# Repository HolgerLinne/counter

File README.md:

# counter
Fast photon counter

A real README will follow soon !

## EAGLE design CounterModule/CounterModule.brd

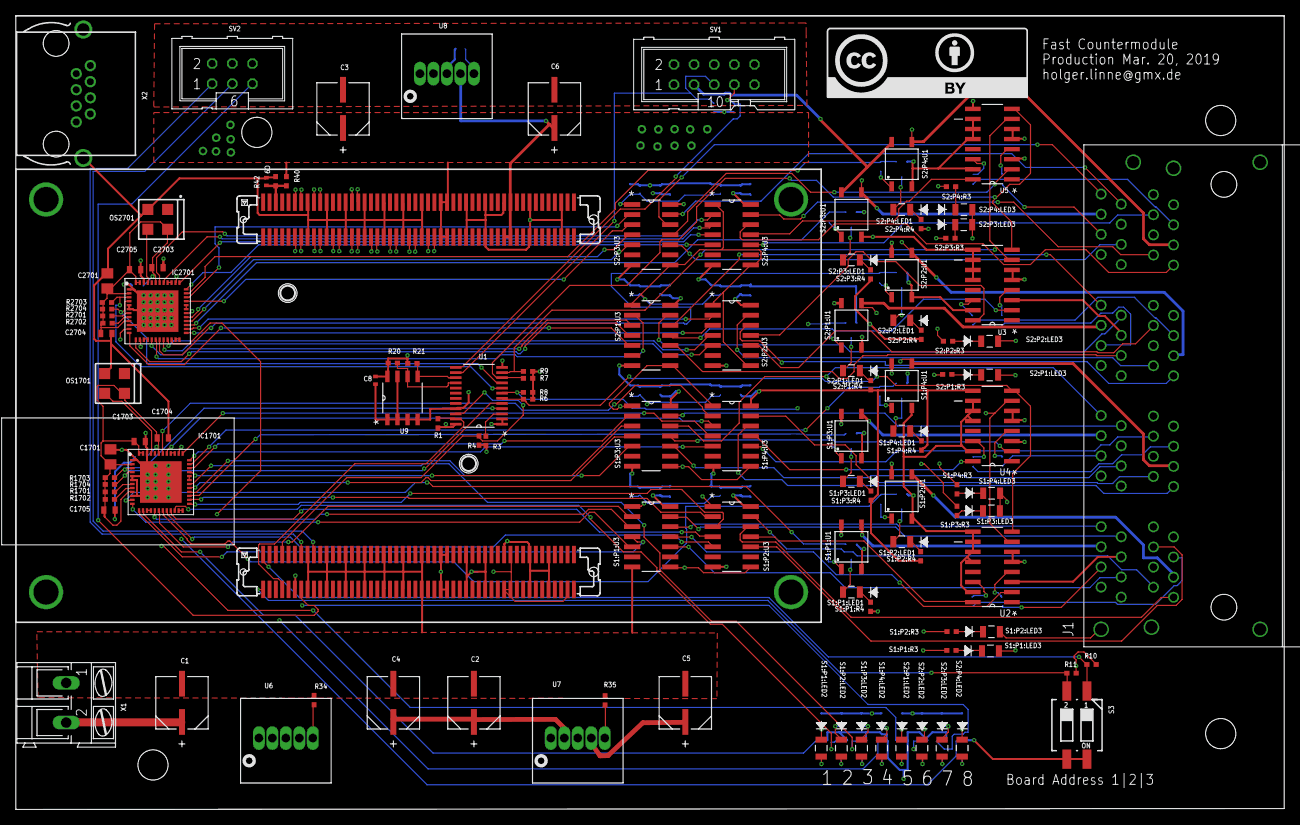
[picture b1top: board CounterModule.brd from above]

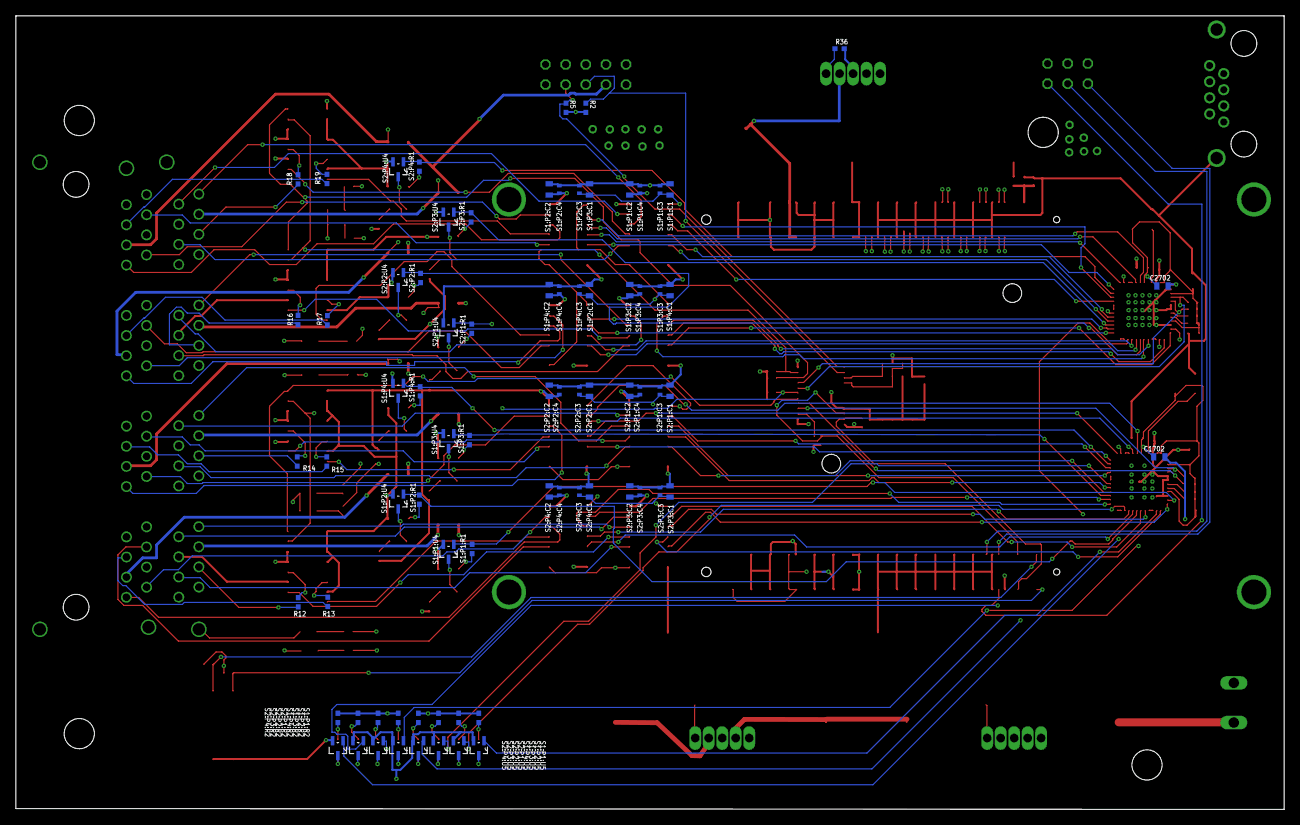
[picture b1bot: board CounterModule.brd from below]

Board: 6 copper layers, 160.0 x 100.1 mm, 192 parts (77 on the bottom side), 217 nets.

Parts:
C1, C2, C3, C4, C5, C6: 100UF; CAPAE660X800N
C8, C9: 100 nF; CAPC1005X60N
C1701, C2701: 10µF; C0805
C1702, C1703, C1704, C1705, C2702, C2703, C2704, C2705: 1uF; CAPC1608X90N
IC1701, IC2701: MAX14830ETM+; QFN50P700X700X80-49N
J1: J1; AMP2X4
MICROZED1: MICROZED_REV_F
OS1701, OS2701: OSC-OE-CFPS-69; 5.0X3.2-4-PAD
R1, R2, R3, R4, R5, R6, R7, R8, R9, R20, R21, R1701, R1702, R1703, R1704, R2701, R2702, R2703, R2704: 4.7 kOhm; RESC1005X40N
R10, R11, R12, R13, R14, R15, R16, R17, R18, R19: 10.2K; RESC1005X40N
R34: 267 OHM; RESC1005X40N
R35: 432 OHM; RESC1005X40N
R36: 619 OHM; RESC1005X40N
R40: 1.02K; RESC1005X40N
R42: 3.92K; RESC1005X40N
S1:P1:C1, S1:P1:C2, S1:P2:C1, S1:P2:C2, S1:P3:C1, S1:P3:C2, S1:P4:C1, S1:P4:C2, S2:P1:C1, S2:P1:C2, S2:P2:C1, S2:P2:C2, S2:P3:C1, S2:P3:C2, S2:P4:C1, S2:P4:C2: 1uF; CAPC1608X90N
S1:P1:C3, S1:P1:C4, S1:P2:C3, S1:P2:C4, S1:P3:C3, S1:P3:C4, S1:P4:C3, S1:P4:C4, S2:P1:C3, S2:P1:C4, S2:P2:C3, S2:P2:C4, S2:P3:C3, S2:P3:C4, S2:P4:C3, S2:P4:C4: 100 nF; CAPC1005X60N
S1:P1:LED1, S1:P2:LED1, S1:P3:LED1, S1:P4:LED1, S2:P1:LED1, S2:P2:LED1, S2:P3:LED1, S2:P4:LED1: CMD17-21VGC_TR8; LED_CMD17-21VGC_TR8
S1:P1:LED2, S1:P2:LED2, S1:P3:LED2, S1:P4:LED2, S2:P1:LED2, S2:P2:LED2, S2:P3:LED2, S2:P4:LED2: CMD17-21VRC_TR8; LED_CMD17-21VRC_TR8
S1:P1:LED3, S1:P2:LED3, S1:P3:LED3, S1:P4:LED3, S2:P1:LED3, S2:P2:LED3, S2:P3:LED3, S2:P4:LED3: CMD17-21VYC_TR8; LED_CMD17-21VYC_TR8
S1:P1:R1, S1:P2:R1, S1:P3:R1, S1:P4:R1, S2:P1:R1, S2:P2:R1, S2:P3:R1, S2:P4:R1: 1K21; RESC1005X40N
S1:P1:R2, S1:P2:R2, S1:P3:R2, S1:P4:R2, S2:P1:R2, S2:P2:R2, S2:P3:R2, S2:P4:R2: 348 OHM; RESC1005X40N
S1:P1:R3, S1:P2:R3, S1:P3:R3, S1:P4:R3, S2:P1:R3, S2:P2:R3, S2:P3:R3, S2:P4:R3: 2K; RESC1005X40N
S1:P1:R4, S1:P2:R4, S1:P3:R4, S1:P4:R4, S2:P1:R4, S2:P2:R4, S2:P3:R4, S2:P4:R4: 124 OHM; RESC1005X40N
S1:P1:U1, S1:P2:U1, S1:P3:U1, S1:P4:U1, S2:P1:U1, S2:P2:U1, S2:P3:U1, S2:P4:U1: CPC1002N; 4-SOP
S1:P1:U3, S1:P2:U3, S1:P3:U3, S1:P4:U3, S2:P1:U3, S2:P2:U3, S2:P3:U3, S2:P4:U3: TXS0104ED; SOIC127P600X175-14N
S1:P1:U4, S1:P1:U5, S1:P2:U4, S1:P2:U5, S1:P3:U4, S1:P3:U5, S1:P4:U4, S1:P4:U5, S2:P1:U4, S2:P1:U5, S2:P2:U4, S2:P2:U5, S2:P3:U4, S2:P3:U5, S2:P4:U4, S2:P4:U5: BSS138BK; SOT65P210X110-3N
S3: 219-02; CTS-219-02
SV1: SV1; ML10
SV2: SV2; ML6
U1: PCA9547PW; SOP65P640X110-24N
U2, U3, U4, U5: AD5242BRZ100; SOIC127P600X175-16N
U6, U7, U8: PTR08060WVD; TI_PTR08060WVD
U9: 24AA02E48-I/SN; SOIC127P600X175-8N
X1: X1; AK300/2
X2: 0446200002

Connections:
!BRD_ADR0: MICROZED1.JX2_1, R10.2, S3.1
!BRD_ADR1: MICROZED1.JX2_2, R11.2, S3.2
+2V5: C6.1, MICROZED1.JX1_78, MICROZED1.JX1_79, MICROZED1.JX1_80, U8.4
+3V3: C5.1, C8.1, C1701.2, C1702.1, C1703.1, C1704.1, C1705.1, C2701.2, C2702.1, C2703.1, C2704.1, C2705.1, IC1701.2, IC1701.9, IC1701.43, IC1701.47, IC1701.48, IC2701.2, IC2701.9, IC2701.43, IC2701.47, IC2701.48, MICROZED1.JX2_78, MICROZED1.JX2_79, MICROZED1.JX2_80, MICROZED1.JX2_98, OS1701.4, OS2701.4, R1.2, R3.2, R4.2, R10.1, R11.1, R20.1, R21.2, R1701.2, R1702.2, R1703.1, R1704.1, R2701.2, R2702.2, R2703.1, R2704.1, S1:P1:C1.1, S1:P1:C3.1, S1:P1:U3.1, S1:P1:U3.8, S1:P2:C1.1, S1:P2:C3.1, S1:P2:U3.1, S1:P2:U3.8, S1:P3:C1.1, S1:P3:C3.1, S1:P3:U3.1, S1:P3:U3.8, S1:P4:C1.1, S1:P4:C3.1, S1:P4:U3.1, S1:P4:U3.8, S2:P1:C1.1, S2:P1:C3.1, S2:P1:U3.1, S2:P1:U3.8, S2:P2:C1.1, S2:P2:C3.1, S2:P2:U3.1, S2:P2:U3.8, S2:P3:C1.1, S2:P3:C3.1, S2:P3:U3.1, S2:P3:U3.8, S2:P4:C1.1, S2:P4:C3.1, S2:P4:U3.1, S2:P4:U3.8, U1.24, U7.4, U9.8
+5V: C2.1, C3.1, C4.1, MICROZED1.JX1_57, MICROZED1.JX1_58, MICROZED1.JX1_59, MICROZED1.JX1_60, MICROZED1.JX2_12, MICROZED1.JX2_57, MICROZED1.JX2_58, MICROZED1.JX2_59, MICROZED1.JX2_60, R2.2, R5.2, R6.1, R7.1, R8.1, R9.1, R40.2, S1:P1:C2.1, S1:P1:C4.1, S1:P1:R2.2, S1:P1:R4.2, S1:P1:U3.14, S1:P2:C2.1, S1:P2:C4.1, S1:P2:R2.2, S1:P2:R4.2, S1:P2:U3.14, S1:P3:C2.1, S1:P3:C4.1, S1:P3:R2.2, S1:P3:R4.2, S1:P3:U3.14, S1:P4:C2.1, S1:P4:C4.1, S1:P4:R2.2, S1:P4:R4.2, S1:P4:U3.14, S2:P1:C2.1, S2:P1:C4.1, S2:P1:R2.2, S2:P1:R4.2, S2:P1:U3.14, S2:P2:C2.1, S2:P2:C4.1, S2:P2:R2.2, S2:P2:R4.2, S2:P2:U3.14, S2:P3:C2.1, S2:P3:C4.1, S2:P3:R2.2, S2:P3:R4.2, S2:P3:U3.14, S2:P4:C2.1, S2:P4:C4.1, S2:P4:R2.2, S2:P4:R4.2, S2:P4:U3.14, SV1.1, U2.5, U2.6, U3.5, U3.6, U4.5, U4.6, U4.9, U5.5, U5.6, U5.9, U6.4, U7.2, U8.2
+12V: C1.1, S1:P1:U1.4, S1:P2:U1.4, S1:P3:U1.4, S1:P4:U1.4, S2:P1:U1.4, S2:P2:U1.4, S2:P3:U1.4, S2:P4:U1.4, SV1.3, U6.2, X1.2
C1_N: J1.P1-7, MICROZED1.JX1_14
C1_P: J1.P1-8, MICROZED1.JX1_12
C2_N: J1.P2-7, MICROZED1.JX1_20
C2_P: J1.P2-8, MICROZED1.JX1_18
C3_N: J1.P3-7, MICROZED1.JX1_26
C3_P: J1.P3-8, MICROZED1.JX1_24
C4_N: J1.P4-7, MICROZED1.JX1_32
C4_P: J1.P4-8, MICROZED1.JX1_30
C5_N: J1.P5-7, MICROZED1.JX1_38
C5_P: J1.P5-8, MICROZED1.JX1_36
C6_N: J1.P6-7, MICROZED1.JX1_44
C6_P: J1.P6-8, MICROZED1.JX1_42
C7_N: J1.P7-7, MICROZED1.JX1_50
C7_P: J1.P7-8, MICROZED1.JX1_48
C8_N: J1.P8-7, MICROZED1.JX1_56
C8_P: J1.P8-8, MICROZED1.JX1_54
CLK1: J1.P1-6, S1:P1:U3.10
CLK2: J1.P2-6, S1:P2:U3.10
CLK3: J1.P3-6, S1:P3:U3.10
CLK4: J1.P4-6, S1:P4:U3.10
CLK5: J1.P5-6, S2:P1:U3.10
CLK6: J1.P6-6, S2:P2:U3.10
CLK7: J1.P7-6, S2:P3:U3.10
CLK8: J1.P8-6, S2:P4:U3.10
GND: C1.2, C2.2, C3.2, C4.2, C5.2, C6.2, C8.2, C9.1, C1701.1, C1702.2, C1703.2, C1704.2, C1705.2, C2701.1, C2702.2, C2703.2, C2704.2, C2705.2, IC1701.1, IC1701.5, IC1701.6, IC1701.10, IC1701.46, IC1701.49, IC2701.1, IC2701.5, IC2701.6, IC2701.10, IC2701.46, IC2701.49, J1.GND@1, J1.GND@2, J1.GND@3, J1.GND@4, J1.GND@5, J1.GND@6, J1.P1-4, J1.P2-4, J1.P3-4, J1.P4-4, J1.P5-4, J1.P6-4, J1.P7-4, J1.P8-4, MICROZED1.JX1_15, MICROZED1.JX1_16, MICROZED1.JX1_21, MICROZED1.JX1_22, MICROZED1.JX1_27, MICROZED1.JX1_28, MICROZED1.JX1_33, MICROZED1.JX1_34, MICROZED1.JX1_39, MICROZED1.JX1_40, MICROZED1.JX1_45, MICROZED1.JX1_46, MICROZED1.JX1_51, MICROZED1.JX1_52, MICROZED1.JX1_65, MICROZED1.JX1_66, MICROZED1.JX1_71, MICROZED1.JX1_72, MICROZED1.JX1_77, MICROZED1.JX1_85, MICROZED1.JX1_86, MICROZED1.JX1_95, MICROZED1.JX1_96, MICROZED1.JX2_15, MICROZED1.JX2_16, MICROZED1.JX2_21, MICROZED1.JX2_22, MICROZED1.JX2_27, MICROZED1.JX2_28, MICROZED1.JX2_33, MICROZED1.JX2_34, MICROZED1.JX2_39, MICROZED1.JX2_40, MICROZED1.JX2_45, MICROZED1.JX2_46, MICROZED1.JX2_51, MICROZED1.JX2_52, MICROZED1.JX2_65, MICROZED1.JX2_66, MICROZED1.JX2_71, MICROZED1.JX2_72, MICROZED1.JX2_77, MICROZED1.JX2_85, MICROZED1.JX2_86, MICROZED1.JX2_91, MICROZED1.JX2_92, OS1701.2, OS2701.2, R34.1, R35.1, R36.1, R42.1, S1:P1:C1.2, S1:P1:C2.2, S1:P1:C3.2, S1:P1:C4.2, S1:P1:LED3.2, S1:P1:U1.2, S1:P1:U3.7, S1:P1:U4.2, S1:P1:U5.2, S1:P2:C1.2, S1:P2:C2.2, S1:P2:C3.2, S1:P2:C4.2, S1:P2:LED3.2, S1:P2:U1.2, S1:P2:U3.7, S1:P2:U4.2, S1:P2:U5.2, S1:P3:C1.2, S1:P3:C2.2, S1:P3:C3.2, S1:P3:C4.2, S1:P3:LED3.2, S1:P3:U1.2, S1:P3:U3.7, S1:P3:U4.2, S1:P3:U5.2, S1:P4:C1.2, S1:P4:C2.2, S1:P4:C3.2, S1:P4:C4.2, S1:P4:LED3.2, S1:P4:U1.2, S1:P4:U3.7, S1:P4:U4.2, S1:P4:U5.2, S2:P1:C1.2, S2:P1:C2.2, S2:P1:C3.2, S2:P1:C4.2, S2:P1:LED3.2, S2:P1:U1.2, S2:P1:U3.7, S2:P1:U4.2, S2:P1:U5.2, S2:P2:C1.2, S2:P2:C2.2, S2:P2:C3.2, S2:P2:C4.2, S2:P2:LED3.2, S2:P2:U1.2, S2:P2:U3.7, S2:P2:U4.2, S2:P2:U5.2, S2:P3:C1.2, S2:P3:C2.2, S2:P3:C3.2, S2:P3:C4.2, S2:P3:LED3.2, S2:P3:U1.2, S2:P3:U3.7, S2:P3:U4.2, S2:P3:U5.2, S2:P4:C1.2, S2:P4:C2.2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
I2C_SCL: MICROZED1.JX2_7, R4.1, U1.22
I2C_SDA: MICROZED1.JX2_8, R1.1, U1.23
LED1: J1.P1-5, R12.1
LED2: J1.P2-5, R13.1
LED3: J1.P3-5, R14.1
LED4: J1.P4-5, R15.1
LED5: J1.P5-5, R16.1
LED6: J1.P6-5, R17.1
LED7: J1.P7-5, R18.1
LED8: J1.P8-5, R19.1
unnamed: IC2701.3, R2703.2, U1.8
unnamed: IC2701.4, R2704.2, U1.9
unnamed: R3.1, U1.3
unnamed: R16.2, U3.4
unnamed: R17.2, U3.14
unnamed: R19.2, U5.14
unnamed: R18.2, U5.4
unnamed: R12.2, U2.4
unnamed: R13.2, U2.14
unnamed: R15.2, U4.14
unnamed: R14.2, U4.4
unnamed: R34.2, U6.5
unnamed: R36.2, U8.5
unnamed: R35.2, U7.5
PWR1: J1.P1-3, S1:P1:R3.2, S1:P1:U1.3
PWR2: J1.P2-3, S1:P2:R3.2, S1:P2:U1.3
PWR3: J1.P3-3, S1:P3:R3.2, S1:P3:U1.3
PWR4: J1.P4-3, S1:P4:R3.2, S1:P4:U1.3
PWR5: J1.P5-3, S2:P1:R3.2, S2:P1:U1.3
PWR6: J1.P6-3, S2:P2:R3.2, S2:P2:U1.3
PWR7: J1.P7-3, S2:P3:R3.2, S2:P3:U1.3
PWR8: J1.P8-3, S2:P4:R3.2, S2:P4:U1.3
PWR_EN: C9.2, MICROZED1.JX1_5, R40.1, R42.2
REXT1: S1:P1:U3.11, U2.2
REXT2: S1:P2:U3.11, U2.16
REXT3: S1:P3:U3.11, U4.2
REXT4: S1:P4:U3.11, U4.16
REXT5: S2:P1:U3.11, U3.2
REXT6: S2:P2:U3.11, U3.16
REXT7: S2:P3:U3.11, U5.2
REXT8: S2:P4:U3.11, U5.16
RX1: J1.P1-1, S1:P1:U3.12
RX2: J1.P2-1, S1:P2:U3.12
RX3: J1.P3-1, S1:P3:U3.12
RX4: J1.P4-1, S1:P4:U3.12
RX5: J1.P5-1, S2:P1:U3.12
RX6: J1.P6-1, S2:P2:U3.12
RX7: J1.P7-1, S2:P3:U3.12
RX8: J1.P8-1, S2:P4:U3.12
S1:!IRQ: IC1701.7, R1701.1
S1:GPIO0: IC1701.11, S1:P1:R1.2, S1:P1:U4.1
S1:GPIO1: IC1701.12, S1:P1:U3.5
S1:GPIO2: IC1701.13, S1:P1:U3.4
S1:GPIO3: IC1701.14, S1:P1:U5.1
S1:GPIO4: IC1701.19, S1:P2:R1.2, S1:P2:U4.1
S1:GPIO5: IC1701.20, S1:P2:U3.5
S1:GPIO7: IC1701.22, S1:P2:U5.1
S1:GPIO8: IC1701.27, S1:P3:R1.2, S1:P3:U4.1
S1:GPIO9: IC1701.28, S1:P3:U3.5
S1:GPIO10: IC1701.29, S1:P3:U3.4
S1:GPIO11: IC1701.30, S1:P3:U5.1
S1:GPIO12: IC1701.35, S1:P4:R1.2, S1:P4:U4.1
S1:GPIO13: IC1701.36, S1:P4:U3.5
S1:GPIO14: IC1701.37, S1:P4:U3.4
S1:GPIO15: IC1701.38, S1:P4:U5.1
S1:GPIUO6: IC1701.21, S1:P2:U3.4
S1:N$1: IC1701.15, IC1701.16
S1:N$2: IC1701.23, IC1701.24
S1:N$3: IC1701.31, IC1701.32
S1:N$4: IC1701.39, IC1701.40
S1:N$5: IC1701.8, R1702.1
S1:N$6: IC1701.45, OS1701.3
S1:P1:N$1: S1:P1:LED1.1, S1:P1:R4.1
S1:P1:N$2: S1:P1:LED2.1, S1:P1:R2.1
S1:P1:N$3: S1:P1:R1.1, S1:P1:U1.1
S1:P1:N$4: S1:P1:LED1.2, S1:P1:U4.3
S1:P1:N$5: S1:P1:LED2.2, S1:P1:U5.3
S1:P1:N$6: S1:P1:LED3.1, S1:P1:R3.1
S1:P2:N$1: S1:P2:LED1.1, S1:P2:R4.1
S1:P2:N$2: S1:P2:LED2.1, S1:P2:R2.1
S1:P2:N$3: S1:P2:R1.1, S1:P2:U1.1
S1:P2:N$4: S1:P2:LED1.2, S1:P2:U4.3
S1:P2:N$5: S1:P2:LED2.2, S1:P2:U5.3
S1:P2:N$6: S1:P2:LED3.1, S1:P2:R3.1
S1:P3:N$1: S1:P3:LED1.1, S1:P3:R4.1
S1:P3:N$2: S1:P3:LED2.1, S1:P3:R2.1
S1:P3:N$3: S1:P3:R1.1, S1:P3:U1.1
S1:P3:N$4: S1:P3:LED1.2, S1:P3:U4.3
S1:P3:N$5: S1:P3:LED2.2, S1:P3:U5.3
S1:P3:N$6: S1:P3:LED3.1, S1:P3:R3.1
S1:P4:N$1: S1:P4:LED1.1, S1:P4:R4.1
S1:P4:N$2: S1:P4:LED2.1, S1:P4:R2.1
S1:P4:N$3: S1:P4:R1.1, S1:P4:U1.1
S1:P4:N$4: S1:P4:LED1.2, S1:P4:U4.3
S1:P4:N$5: S1:P4:LED2.2, S1:P4:U5.3
S1:P4:N$6: S1:P4:LED3.1, S1:P4:R3.1
S1:RX0: IC1701.17, S1:P1:U3.3
S1:RX1: IC1701.25, S1:P2:U3.3
S1:RX2: IC1701.33, S1:P3:U3.3
S1:RX3: IC1701.41, S1:P4:U3.3
S1:TX0: IC1701.18, S1:P1:U3.2
S1:TX1: IC1701.26, S1:P2:U3.2
S1:TX2: IC1701.34, S1:P3:U3.2
S1:TX3: IC1701.42, S1:P4:U3.2
S2:!IRQ: IC2701.7, R2701.1
S2:GPIO0: IC2701.11, S2:P1:R1.2, S2:P1:U4.1
S2:GPIO1: IC2701.12, S2:P1:U3.5
S2:GPIO2: IC2701.13, S2:P1:U3.4
S2:GPIO3: IC2701.14, S2:P1:U5.1
S2:GPIO4: IC2701.19, S2:P2:R1.2, S2:P2:U4.1
S2:GPIO5: IC2701.20, S2:P2:U3.5
S2:GPIO7: IC2701.22, S2:P2:U5.1
S2:GPIO8: IC2701.27, S2:P3:R1.2, S2:P3:U4.1
S2:GPIO9: IC2701.28, S2:P3:U3.5
S2:GPIO10: IC2701.29, S2:P3:U3.4
S2:GPIO11: IC2701.30, S2:P3:U5.1
S2:GPIO12: IC2701.35, S2:P4:R1.2, S2:P4:U4.1
S2:GPIO13: IC2701.36, S2:P4:U3.5
S2:GPIO14: IC2701.37, S2:P4:U3.4
S2:GPIO15: IC2701.38, S2:P4:U5.1
S2:GPIUO6: IC2701.21, S2:P2:U3.4
S2:N$1: IC2701.15, IC2701.16
S2:N$2: IC2701.23, IC2701.24
S2:N$3: IC2701.31, IC2701.32
S2:N$4: IC2701.39, IC2701.40
S2:N$5: IC2701.8, R2702.1
S2:N$6: IC2701.45, OS2701.3
S2:P1:N$1: S2:P1:LED1.1, S2:P1:R4.1
S2:P1:N$2: S2:P1:LED2.1, S2:P1:R2.1
S2:P1:N$3: S2:P1:R1.1, S2:P1:U1.1
S2:P1:N$4: S2:P1:LED1.2, S2:P1:U4.3
S2:P1:N$5: S2:P1:LED2.2, S2:P1:U5.3
S2:P1:N$6: S2:P1:LED3.1, S2:P1:R3.1
S2:P2:N$1: S2:P2:LED1.1, S2:P2:R4.1
S2:P2:N$2: S2:P2:LED2.1, S2:P2:R2.1
S2:P2:N$3: S2:P2:R1.1, S2:P2:U1.1
S2:P2:N$4: S2:P2:LED1.2, S2:P2:U4.3
S2:P2:N$5: S2:P2:LED2.2, S2:P2:U5.3
S2:P2:N$6: S2:P2:LED3.1, S2:P2:R3.1
S2:P3:N$1: S2:P3:LED1.1, S2:P3:R4.1
S2:P3:N$2: S2:P3:LED2.1, S2:P3:R2.1
S2:P3:N$3: S2:P3:R1.1, S2:P3:U1.1
S2:P3:N$4: S2:P3:LED1.2, S2:P3:U4.3
S2:P3:N$5: S2:P3:LED2.2, S2:P3:U5.3
S2:P3:N$6: S2:P3:LED3.1, S2:P3:R3.1
S2:P4:N$1: S2:P4:LED1.1, S2:P4:R4.1
S2:P4:N$2: S2:P4:LED2.1, S2:P4:R2.1
S2:P4:N$3: S2:P4:R1.1, S2:P4:U1.1
S2:P4:N$4: S2:P4:LED1.2, S2:P4:U4.3
S2:P4:N$5: S2:P4:LED2.2, S2:P4:U5.3
S2:P4:N$6: S2:P4:LED3.1, S2:P4:R3.1
S2:RX0: IC2701.17, S2:P1:U3.3
S2:RX1: IC2701.25, S2:P2:U3.3
S2:RX2: IC2701.33, S2:P3:U3.3
S2:RX3: IC2701.41, S2:P4:U3.3
S2:TX0: IC2701.18, S2:P1:U3.2
S2:TX1: IC2701.26, S2:P2:U3.2
S2:TX2: IC2701.34, S2:P3:U3.2
S2:TX3: IC2701.42, S2:P4:U3.2
SC0: IC1701.4, R1704.2, U1.5
SC1: R8.2, U1.7, U2.7, U4.7
SC3: R9.2, U1.11, U3.7, U5.7
SC4: R2.1, SV1.5, U1.14
SC5: R20.2, U1.16, U9.6
SD0: IC1701.3, R1703.2, U1.4
SD1: R6.2, U1.6, U2.8, U4.8
SD3: R7.2, U1.10, U3.8, U5.8
SD4: R5.1, SV1.7, U1.13
SD5: R21.1, U1.15, U9.5
SHOT_N: MICROZED1.JX1_29, X2.8
SHOT_P: MICROZED1.JX1_31, X2.7
SHOT_S: MICROZED1.JX2_14, SV2.5
T1_N: MICROZED1.JX1_13, X2.2
T1_P: MICROZED1.JX1_11, X2.1
T1_S: MICROZED1.JX2_13, SV2.1
T10_N: MICROZED1.JX1_19, X2.5
T10_P: MICROZED1.JX1_17, X2.4
T10_S: MICROZED1.JX2_17, SV2.3
TX1: J1.P1-2, S1:P1:U3.13
TX2: J1.P2-2, S1:P2:U3.13
TX3: J1.P3-2, S1:P3:U3.13
TX4: J1.P4-2, S1:P4:U3.13
TX5: J1.P5-2, S2:P1:U3.13
TX6: J1.P6-2, S2:P2:U3.13
TX7: J1.P7-2, S2:P3:U3.13
TX8: J1.P8-2, S2:P4:U3.13

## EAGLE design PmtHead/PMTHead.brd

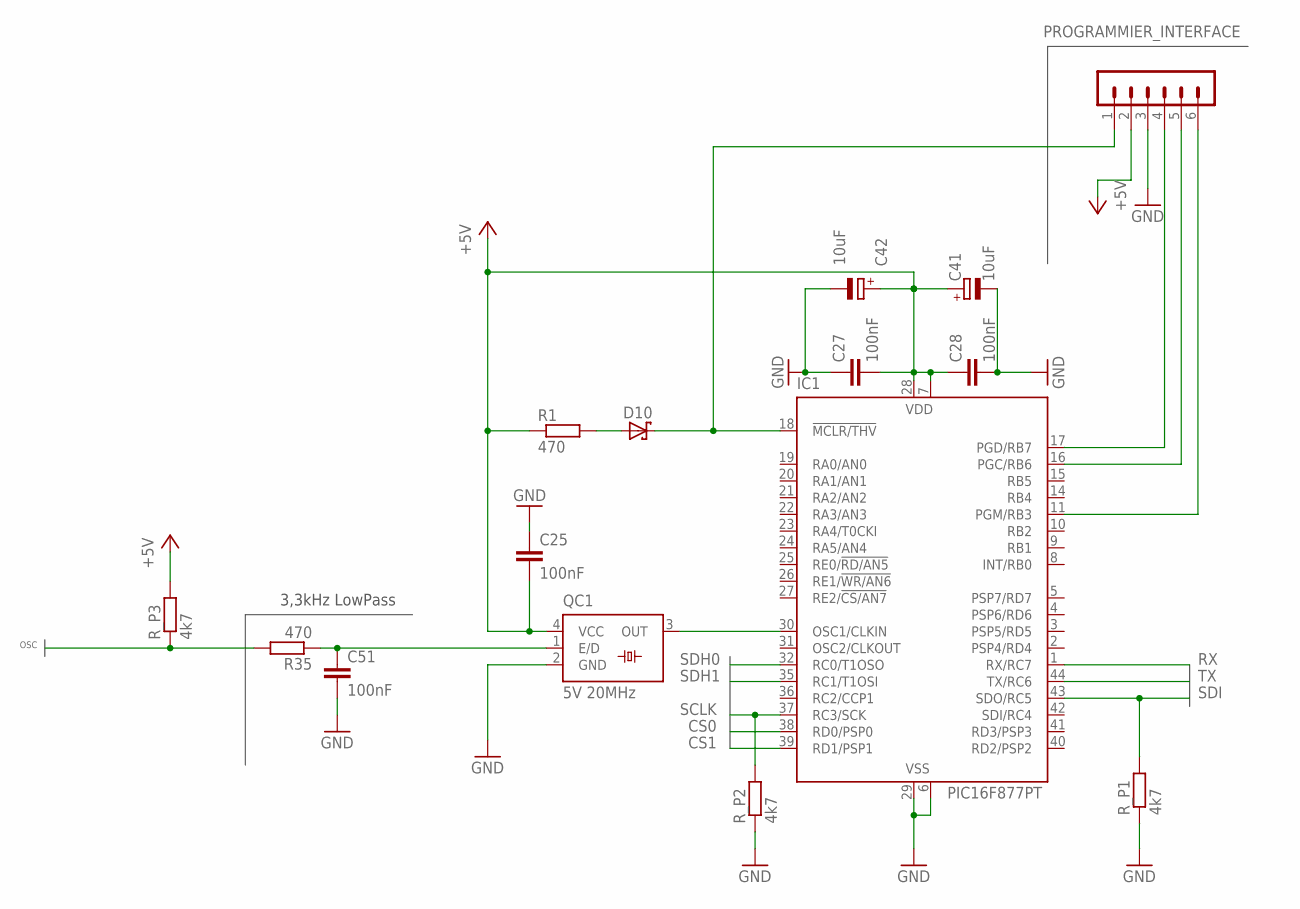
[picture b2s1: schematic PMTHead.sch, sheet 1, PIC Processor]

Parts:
C25, C27, C28, C51: 100nF; C0805
C41, C42: 10uF; C/6032-28R
D10: DIODE_BAT750; SOT23
IC1: PIC16F877PT; TQFP44
PROGRAMMIER_INTERFACE: MA06-1
QC1: 5V 20MHz; SM77H
R1, R35: 470; R0805
R_P1, R_P2, R_P3: 4k7; R0805

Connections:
+5V: C25.2, C27.2, C28.1, C41.+, C42.+, IC1.7 (VDD), IC1.28 (VDD), PROGRAMMIER_INTERFACE.2, QC1.4 (VCC), R1.1, R_P3.2; also elsewhere on the board
CS0: IC1.38 (RD0/PSP0); also elsewhere on the board
CS1: IC1.39 (RD1/PSP1); also elsewhere on the board
GND: C25.1, C27.1, C28.2, C41.-, C42.-, C51.2, IC1.6 (VSS), IC1.29 (VSS), PROGRAMMIER_INTERFACE.3, QC1.2 (GND), R_P1.1, R_P2.1; also elsewhere on the board
unnamed: IC1.11 (PGM/RB3), PROGRAMMIER_INTERFACE.6
unnamed: IC1.16 (PGC/RB6), PROGRAMMIER_INTERFACE.5
unnamed: IC1.17 (PGD/RB7), PROGRAMMIER_INTERFACE.4
unnamed: D10.3 (C), IC1.18 (!MCLR/THV), PROGRAMMIER_INTERFACE.1
unnamed: D10.1 (A), R1.2
unnamed: C51.1, QC1.1 (E/D), R35.1
OSC: R35.2, R_P3.1; also elsewhere on the board
OSC_OUT: IC1.30 (OSC1/CLKIN), QC1.3 (OUT)
RX: IC1.1 (RX/RC7); also elsewhere on the board
SCLK: IC1.37 (RC3/SCK), R_P2.2; also elsewhere on the board
SDH0: IC1.32 (RC0/T1OSO); also elsewhere on the board
SDH1: IC1.35 (RC1/T1OSI); also elsewhere on the board
SDI: IC1.43 (SDO/RC5), R_P1.2; also elsewhere on the board
TX: IC1.44 (TX/RC6); also elsewhere on the board

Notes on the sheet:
3,3kHz LowPass

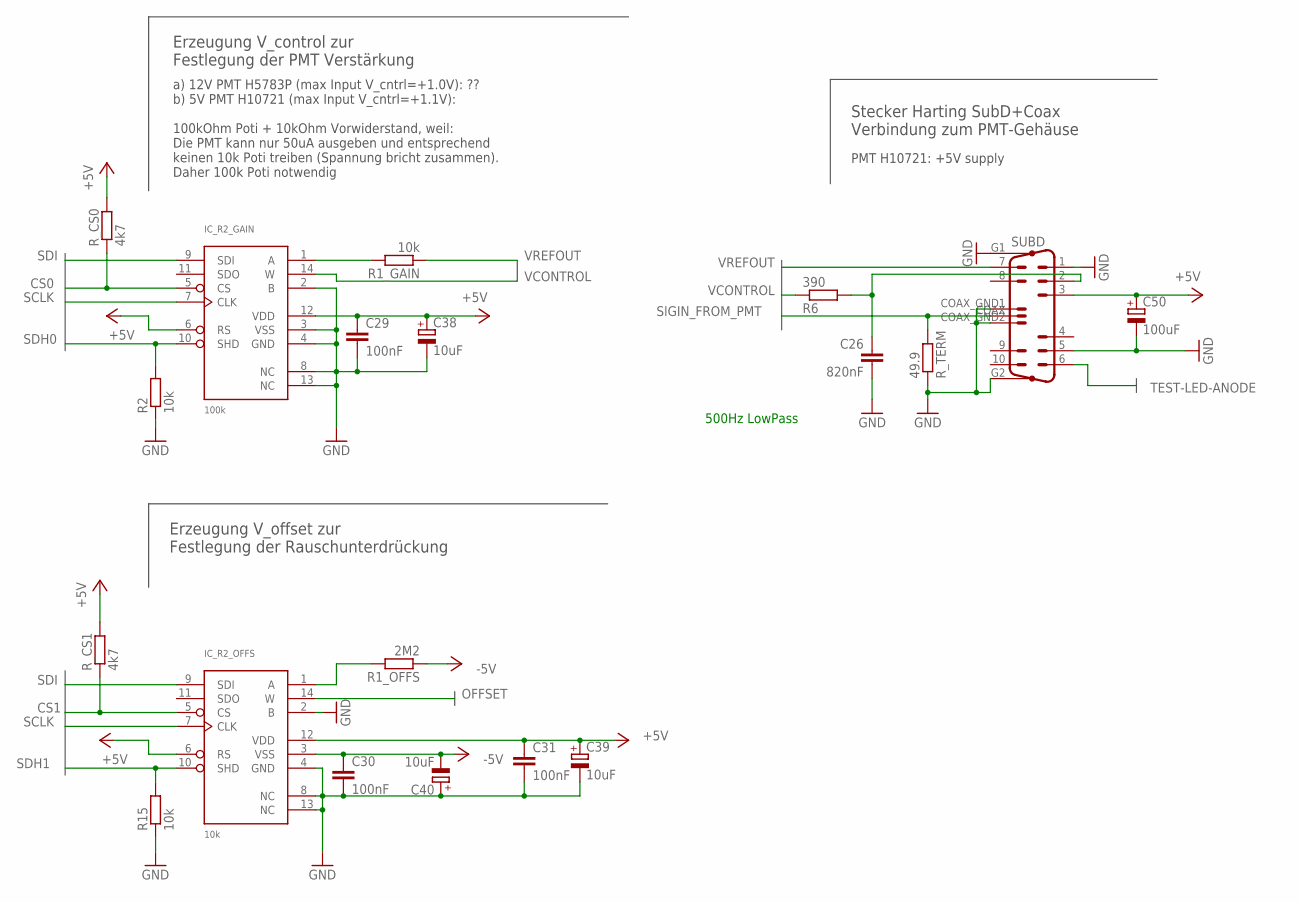
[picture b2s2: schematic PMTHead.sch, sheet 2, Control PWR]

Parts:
C26: 820nF; C1206
C29, C30, C31: 100nF; C0805
C38, C39, C40: 10uF; C/6032-28R
C50: 100uF; D/7343-31R
IC_R2_GAIN: 100k; TSSOP14
IC_R2_OFFS: 10k; TSSOP14
R1_GAIN, R2, R15: 10k; R0805
R1_OFFS: 2M2; R0805
R6: 390; R0805
R_CS0, R_CS1: 4k7; R0805
R_TERM: 49.9; R0805
SUBD: M15HP

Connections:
+5V: C29.1, C31.1, C38.+, C39.+, C50.+, IC_R2_GAIN.6 (RS), IC_R2_GAIN.12 (VDD), IC_R2_OFFS.6 (RS), IC_R2_OFFS.12 (VDD), R_CS0.2, R_CS1.2, SUBD.3; also elsewhere on the board
-5V: C30.1, C40.-, IC_R2_OFFS.3 (VSS), R1_OFFS.1; also elsewhere on the board
CS0: IC_R2_GAIN.5 (CS), R_CS0.1; also elsewhere on the board
CS1: IC_R2_OFFS.5 (CS), R_CS1.1; also elsewhere on the board
GND: C26.2, C29.2, C30.2, C31.2, C38.-, C39.-, C40.+, C50.-, IC_R2_GAIN.2 (B), IC_R2_GAIN.3 (VSS), IC_R2_GAIN.4 (GND), IC_R2_GAIN.8 (NC), IC_R2_GAIN.13 (NC), IC_R2_OFFS.2 (B), IC_R2_OFFS.4 (GND), IC_R2_OFFS.8 (NC), IC_R2_OFFS.13 (NC), R2.1, R15.1, R_TERM.1, SUBD.1, SUBD.5, SUBD.COAX_GND1, SUBD.COAX_GND2, SUBD.G1, SUBD.G2; also elsewhere on the board
unnamed: IC_R2_GAIN.1 (A), R1_GAIN.2
unnamed: IC_R2_OFFS.1 (A), R1_OFFS.2
unnamed: C26.1, R6.2, SUBD.2
OFFSET: IC_R2_OFFS.14 (W); also elsewhere on the board
SCLK: IC_R2_GAIN.7 (CLK), IC_R2_OFFS.7 (CLK); also elsewhere on the board
SDH0: IC_R2_GAIN.10 (SHD), R2.2; also elsewhere on the board
SDH1: IC_R2_OFFS.10 (SHD), R15.2; also elsewhere on the board
SDI: IC_R2_GAIN.9 (SDI), IC_R2_OFFS.9 (SDI); also elsewhere on the board
SIGIN_FROM_PMT: R_TERM.2, SUBD.COAX; also elsewhere on the board
TEST-LED-ANODE: SUBD.6; also elsewhere on the board
VCONTROL: IC_R2_GAIN.14 (W), R6.1
VREFOUT: R1_GAIN.1, SUBD.7

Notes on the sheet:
a) 12V PMT H5783P (max Input V_cntrl=+1.0V): ?? b) 5V PMT H10721 (max Input V_cntrl=+1.1V): 100kOhm Poti + 10kOhm Vorwiderstand, weil: Die PMT kann nur 50uA ausgeben und entsprechend keinen 10k Poti treiben (Spannung bricht zusammen). Daher 100k Poti notwendig
500Hz LowPass
PMT H10721: +5V supply
Stecker Harting SubD+Coax Verbindung zum PMT-Gehäuse
Erzeugung V_control zur Festlegung der PMT Verstärkung
Erzeugung V_offset zur Festlegung der Rauschunterdrückung

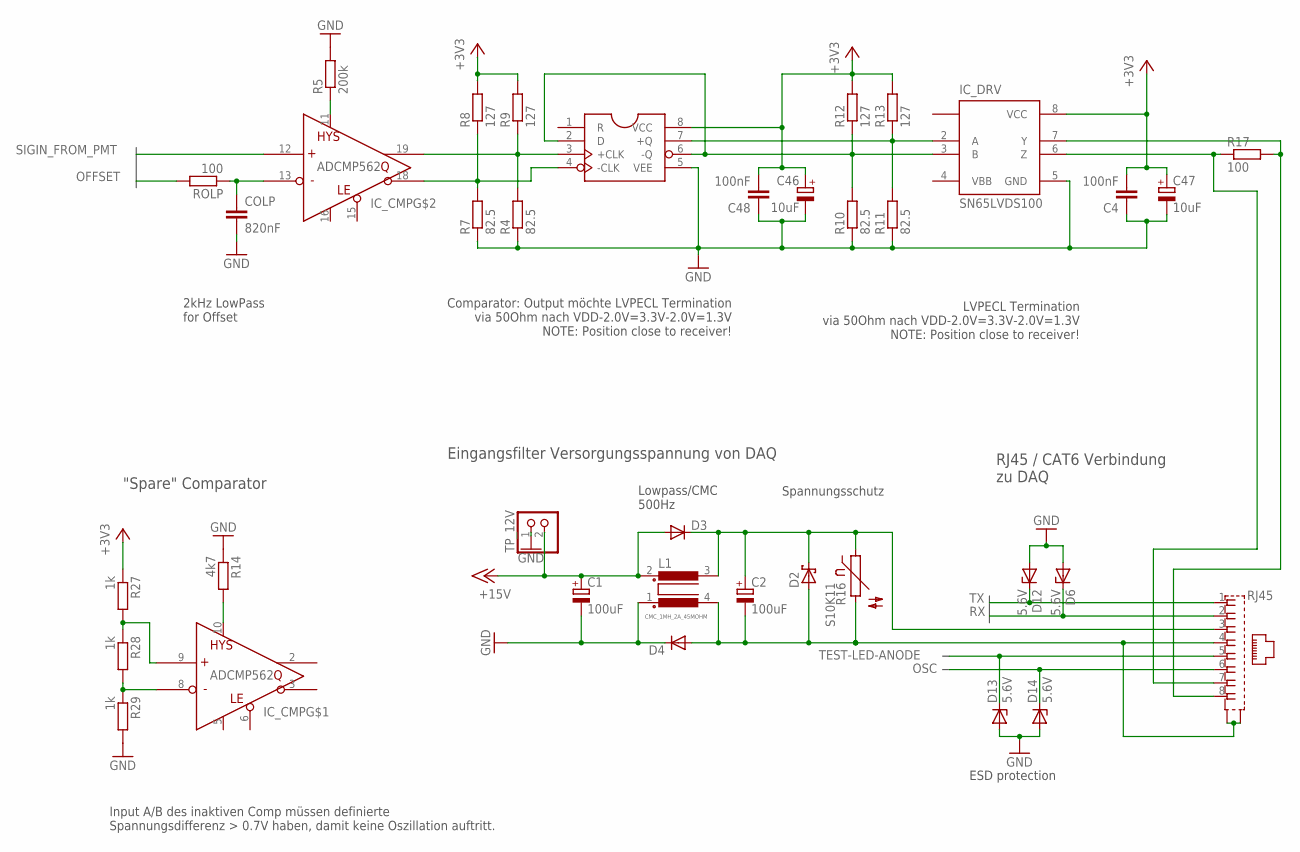
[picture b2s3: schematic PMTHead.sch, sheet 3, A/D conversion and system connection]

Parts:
C1, C2: 100uF; D/7343-31R
C4, C48: 100nF; C0805
C46, C47: 10uF; C/6032-28R
COLP: 820nF; C1206
D2: SCHOTTKY-DIODESMC; SMC
D3, D4: DIODE-SOD80C; SOD80C
D6, D12, D13, D14: 5.6V; MINIMELF
IC_CMP: ADCMP562; QSOP20
IC_DRV: SN65LVDS100; SOP08@1
IC_FLIP: MC100LVEL51; SOP08@1
L1: CMC_1MH_2A_45MOHM; 82721K
R4, R7, R10, R11: 82.5; R0805
R5: 200k; R0805
R8, R9, R12, R13: 127; R0805
R14: 4k7; R0805
R16: S10K11
R17: 100; R0805
R27, R28, R29: 1k; M0805
RJ45: CAT6
ROLP: 100; R0805
TP_12V: PINHD-1X2; 1X02

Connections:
12V_VON_DAQ: C2.+, D2.C, D3.C, L1.3, R16.1, RJ45.3
+3V3: C4.2, C46.+, C47.+, C48.2, IC_DRV.8 (VCC), IC_FLIP.8 (VCC), R8.2, R9.2, R12.2, R13.2, R27.1; also elsewhere on the board
+15V: C1.+, D3.A, L1.2 (4), TP_12V.2; also elsewhere on the board
CMP_OUT1: IC_CMP.19 (+OUT), IC_FLIP.3 (+CLK), R4.2, R9.1
CMP_OUT2: IC_CMP.18 (-OUT), IC_FLIP.4 (-CLK), R7.2, R8.1
DRIVER_OUT1: IC_DRV.7 (Y), R17.2, RJ45.8
DRIVER_OUT2: IC_DRV.6 (Z), R17.1, RJ45.7
FLIPFLOP_OUT1: IC_DRV.3 (B), IC_FLIP.2 (D), IC_FLIP.6 (-Q), R10.2, R12.1
FLIPFLOP_OUT2: IC_DRV.2 (A), IC_FLIP.7 (+Q), R11.2, R13.1
GND: C1.-, C4.1, C46.-, C47.-, C48.1, COLP.2, D4.C, D6.A, D12.A, D13.A, D14.A, IC_DRV.5 (GND), IC_FLIP.5 (VEE), L1.1, R4.1, R5.2, R7.1, R10.1, R11.1, R14.1, R29.2, TP_12V.1; also elsewhere on the board
GND_VON_DAQ: C2.-, D2.A, D4.A, L1.4 (2), R16.2, RJ45.4, RJ45.P$1 (S1), RJ45.P$2 (S2)
unnamed: IC_CMP.11 (HYS), R5.1
unnamed: COLP.1, IC_CMP.13 (-IN), ROLP.1
unnamed: IC_CMP.10 (HYS), R14.2
unnamed: IC_CMP.9 (+IN), R27.2, R28.1
unnamed: IC_CMP.8 (-IN), R28.2, R29.1
OFFSET: ROLP.2; also elsewhere on the board
OSC: D14.C, RJ45.6; also elsewhere on the board
RX: D6.C, RJ45.2; also elsewhere on the board
SIGIN_FROM_PMT: IC_CMP.12 (+IN); also elsewhere on the board
TEST-LED-ANODE: D13.C, RJ45.5; also elsewhere on the board
TX: D12.C, RJ45.1; also elsewhere on the board
VBB: IC_DRV.4 (VBB)

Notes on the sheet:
Spannungsschutz
Lowpass/CMC 500Hz
2kHz LowPass for Offset
Input A/B des inaktiven Comp müssen definierte Spannungsdifferenz > 0.7V haben, damit keine Oszillation auftritt.
Comparator: Output möchte LVPECL Termination via 50Ohm nach VDD-2.0V=3.3V-2.0V=1.3V NOTE: Position close to receiver!
LVPECL Termination via 50Ohm nach VDD-2.0V=3.3V-2.0V=1.3V NOTE: Position close to receiver!
RJ45 / CAT6 Verbindung zu DAQ
Eingangsfilter Versorgungsspannung von DAQ
"Spare" Comparator
ESD protection

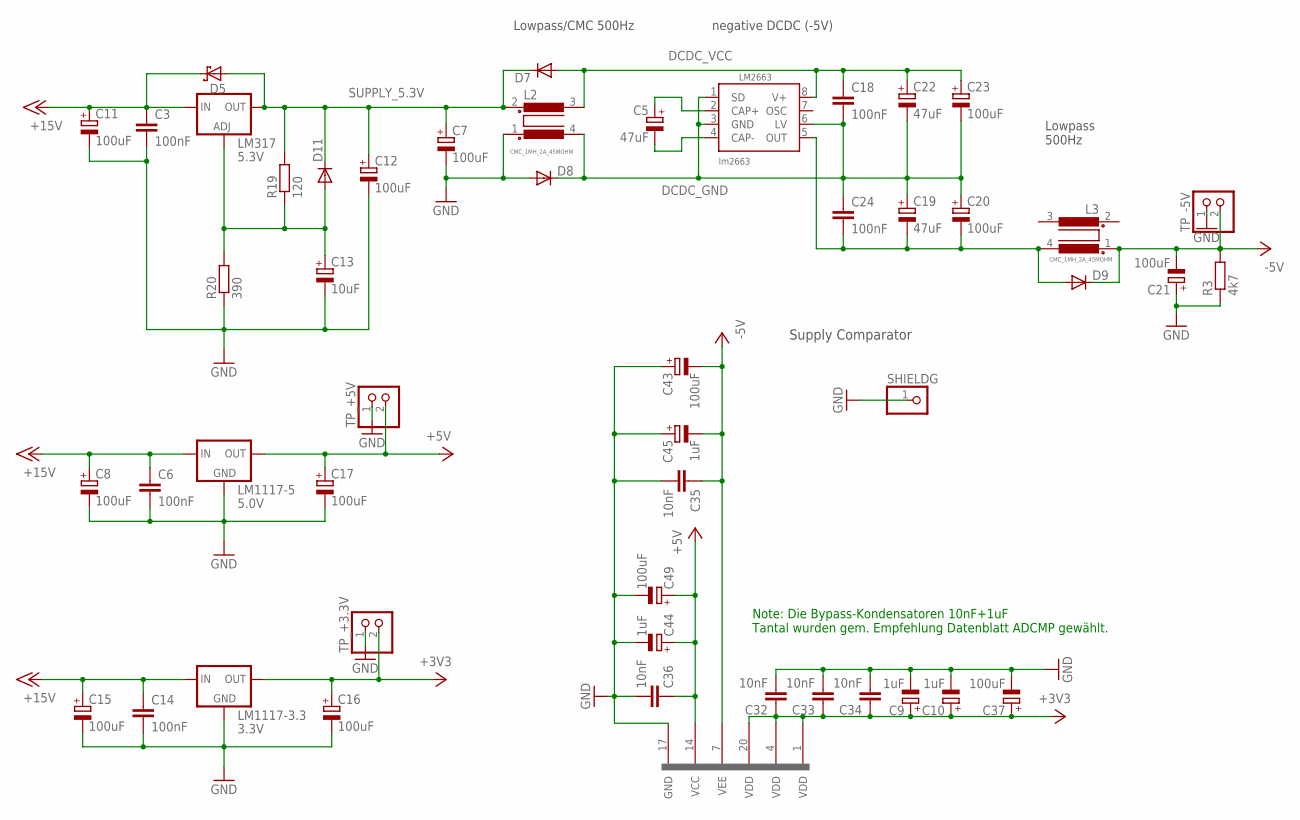
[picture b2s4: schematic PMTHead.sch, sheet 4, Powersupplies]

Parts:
C3, C6, C14, C18, C24: 100nF; C0805
C5, C19, C22: 47uF; D/7343-31R
C7, C8, C11, C12, C15, C16, C17, C20, C21, C23, C37, C43, C49: 100uF; D/7343-31R
C9, C10, C44, C45: 1uF; A/3216-18W
C13: 10uF; C/6032-28R
C32, C33, C34, C35, C36: 10nF; C0805
D5: SCHOTTKY-DIODESMD; SMB
D7, D8, D9, D11: DIODE-SOD80C; SOD80C
IC_CMP: ADCMP562; QSOP20
L2, L3: CMC_1MH_2A_45MOHM; 82721K
LM317: 5.3V; 317TS
LM1117-3.3: 3.3V; 317TS
LM1117-5: 5.0V; 317TS
LM2663: lm2663; SOP08
R3: 4k7; R0805
R19: 120; M0805
R20: 390; R0805
SHIELDG: PINHD-1X1; 1X01
TP_+3.3V, TP_+5V: PINHD-1X2; 1X02
TP_-5V: PINHD-1X2; 1X02

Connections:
+3V3: C9.+, C10.+, C16.+, C32.1, C33.1, C34.1, C37.+, IC_CMP.1 (VDD), IC_CMP.4 (VDD), IC_CMP.20 (VDD), LM1117-3.3.2_OUT (OUT), TP_+3.3V.2; also elsewhere on the board
+5V: C17.+, C36.1, C44.+, C49.+, IC_CMP.14 (VCC), LM1117-5.2_OUT (OUT), TP_+5V.2; also elsewhere on the board
+15V: C3.1, C6.1, C8.+, C11.+, C14.1, C15.+, D5.C, LM317.3 (IN), LM1117-3.3.3_IN (IN), LM1117-5.3_IN (IN); also elsewhere on the board
-5V: C21.-, C35.1, C43.-, C45.-, D9.C, IC_CMP.7 (VEE), L3.1, R3.2, TP_-5V.2; also elsewhere on the board
DCDC_GND: C18.2, C19.+, C20.+, C22.-, C23.-, C24.1, D8.C, L2.4 (2), LM2663.1 (SD), LM2663.3 (GND), LM2663.6 (LV)
DCDC_VCC: C18.1, C22.+, C23.+, D7.A, L2.3, LM2663.8 (V+)
GND: C3.2, C6.2, C7.-, C8.-, C9.-, C10.-, C11.-, C12.-, C13.-, C14.2, C15.-, C16.-, C17.-, C21.+, C32.2, C33.2, C34.2, C35.2, C36.2, C37.-, C43.+, C44.-, C45.+, C49.-, D8.A, IC_CMP.17 (GND), L2.1, LM1117-3.3.1_GND (GND), LM1117-5.1_GND (GND), R3.1, R20.1, SHIELDG.1, TP_+3.3V.1, TP_+5V.1, TP_-5V.1; also elsewhere on the board
LM317_ADJ: C13.+, D11.A, LM317.1 (ADJ), R19.1, R20.2
unnamed: C5.+, LM2663.2 (CAP+)
unnamed: C5.-, LM2663.4 (CAP-)
unnamed: C19.-, C20.-, C24.2, D9.A, L3.4 (2), LM2663.5 (OUT)
SUPPLY_5.3V: C7.+, C12.+, D5.A, D7.C, D11.C, L2.2 (4), LM317.2 (OUT), R19.2

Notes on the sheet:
Lowpass/CMC 500Hz
Lowpass 500Hz
negative DCDC (-5V)
Supply Comparator
Note: Die Bypass-Kondensatoren 10nF+1uF Tantal wurden gem. Empfehlung Datenblatt ADCMP gewählt.

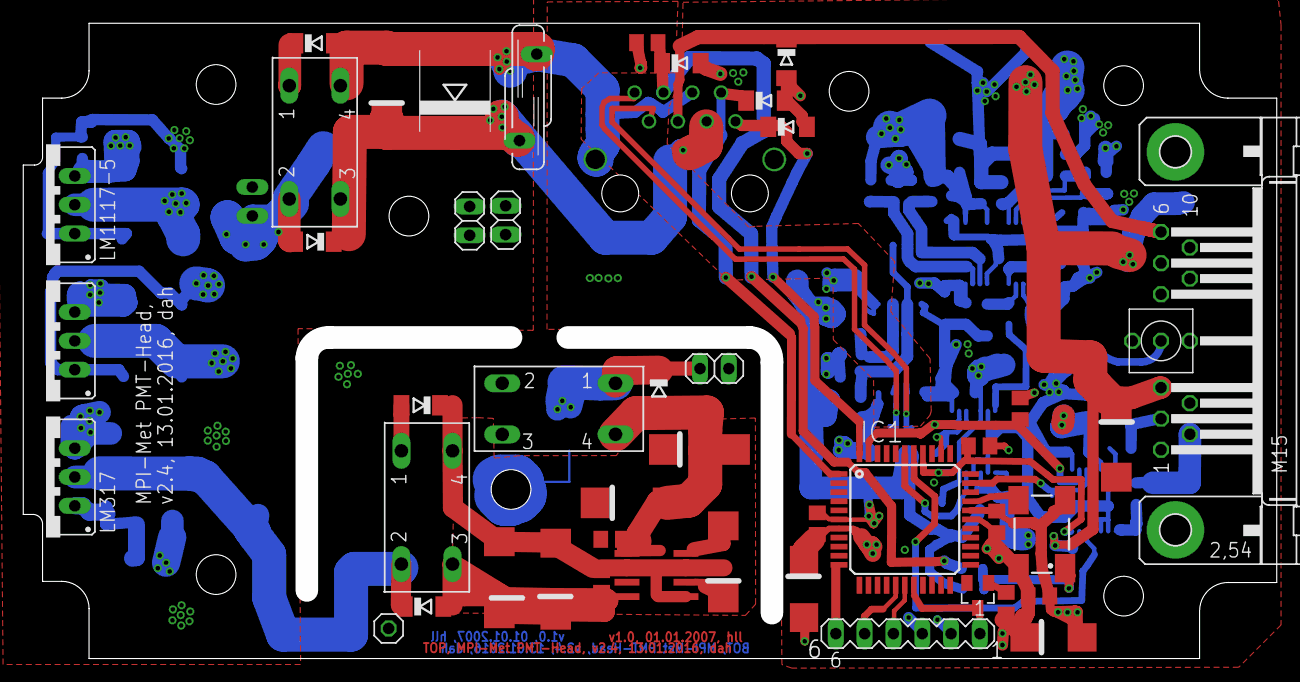
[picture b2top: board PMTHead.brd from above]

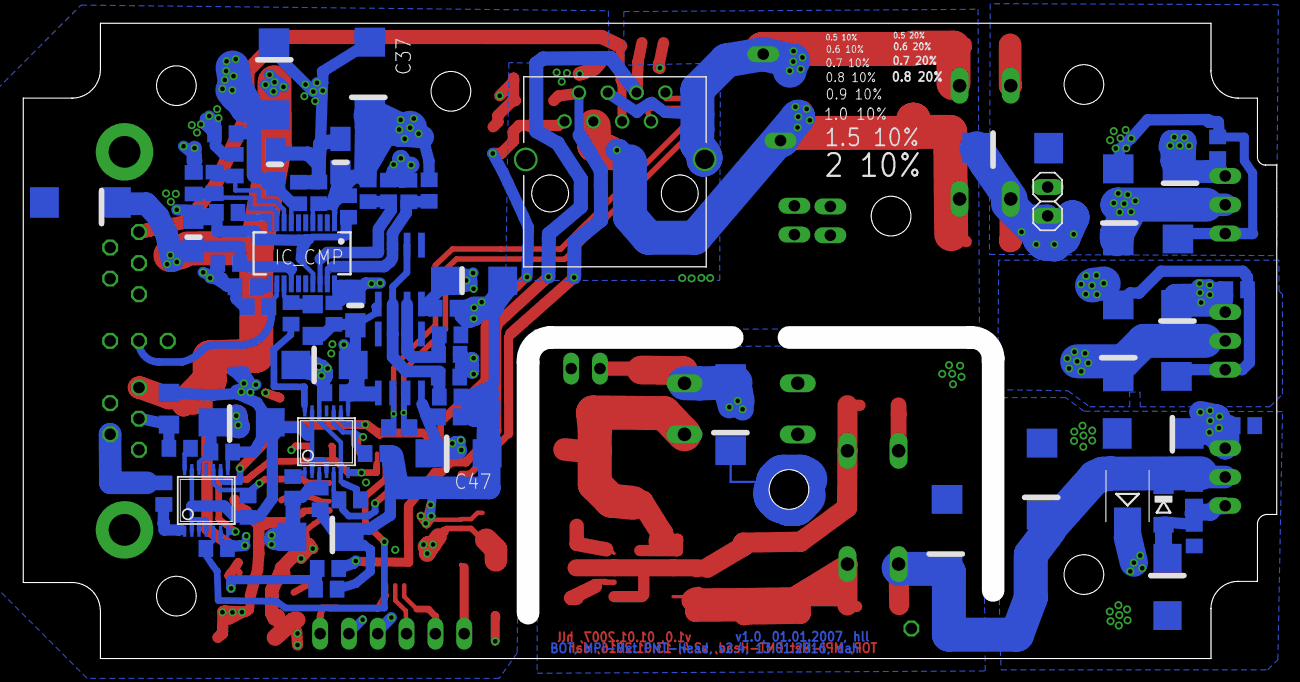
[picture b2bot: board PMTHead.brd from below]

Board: 4 copper layers, 110.5 x 56.0 mm, 119 parts (74 on the bottom side), 49 nets.

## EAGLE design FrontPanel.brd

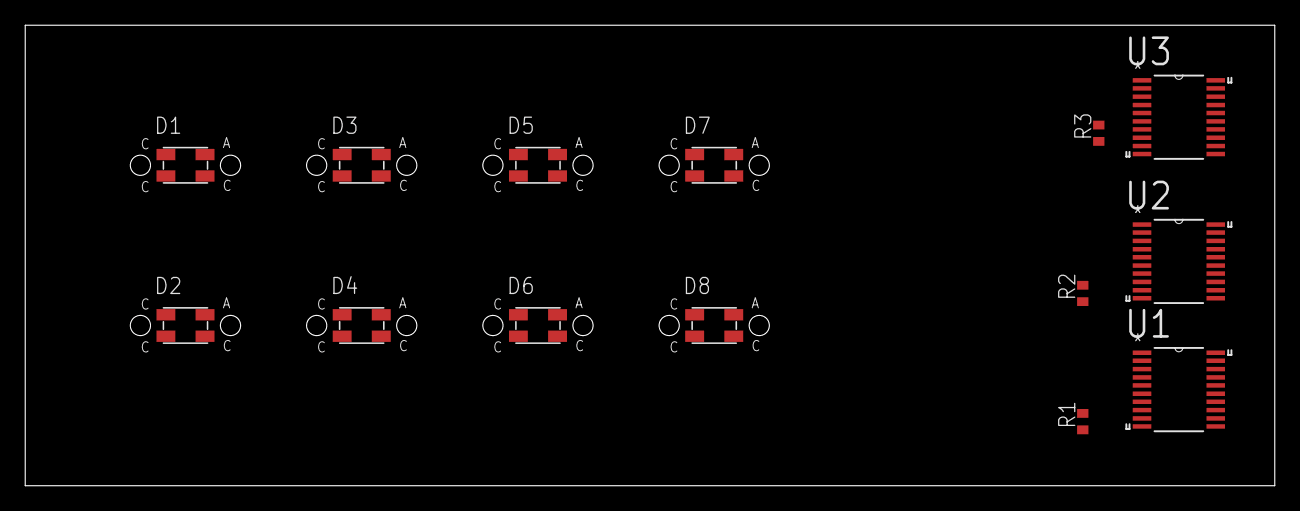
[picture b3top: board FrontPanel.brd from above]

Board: 2 copper layers, 99.0 x 36.5 mm, 14 parts (0 on the bottom side), 32 nets, no tracks yet.

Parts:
D1, D2, D3, D4, D5, D6, D7, D8: WL-SFTW; 3528-COMMON-ANODE
R1, R2, R3: R0402
U1, U2, U3: TLC59108; SOP65P640X120-20N

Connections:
BLUE0: D1.2, U3.6
BLUE1: D2.2, U3.7
BLUE2: D3.2, U3.9
BLUE3: D4.2, U3.10
BLUE4: D5.2, U3.11
BLUE5: D6.2, U3.12
BLUE6: D7.2, U3.14
BLUE7: D8.2, U3.15
GND: R1.1, R2.1, R3.1, U1.2, U1.3, U1.4, U1.5, U1.8, U1.13, U1.16, U2.3, U2.4, U2.5, U2.8, U2.13, U2.16, U3.2, U3.4, U3.5, U3.8, U3.13, U3.16
GREEN0: D1.4, U2.6
GREEN1: D2.4, U2.7
GREEN2: D3.4, U2.9
GREEN3: D4.4, U2.10
GREEN4: D5.4, U2.11
GREEN5: D6.4, U2.12
GREEN6: D7.4, U2.14
GREEN7: D8.4, U2.15
unnamed: R3.2, U3.1
unnamed: R2.2, U2.1
unnamed: R1.2, U1.1
RED0: D1.3, U1.6
RED1: D2.3, U1.7
RED2: D3.3, U1.9
RED3: D4.3, U1.10
RED4: D5.3, U1.11
RED5: D6.3, U1.12
RED6: D7.3, U1.14
RED7: D8.3, U1.15
RESET: U1.17, U2.17, U3.17
SCL: U1.18, U2.18, U3.18
SDA: U1.19, U2.19, U3.19
VCC: D1.1, D2.1, D3.1, D4.1, D5.1, D6.1, D7.1, D8.1, U1.20, U2.2, U2.20, U3.3, U3.20

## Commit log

2017-10-08 Initial commit. Prototype 18/08/2017.
2019-03-16 Prototype 2019/03/16 complete reconstruction.
2019-03-20 Complete restructure of counter-tree. Finished Prototype 03202019.
2019-03-20 Added the sources for the CounterModule library.
2019-03-21 Tuned license file to work as a MarkDown file.

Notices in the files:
PmtHead/PMTHead.sch:
Creative Commons License
Attribution 4.0 International (CC BY 4.0)
parts and their libraries:
WURTH-COLOR_LED-rev1: Copyright: Würth Elektronik
